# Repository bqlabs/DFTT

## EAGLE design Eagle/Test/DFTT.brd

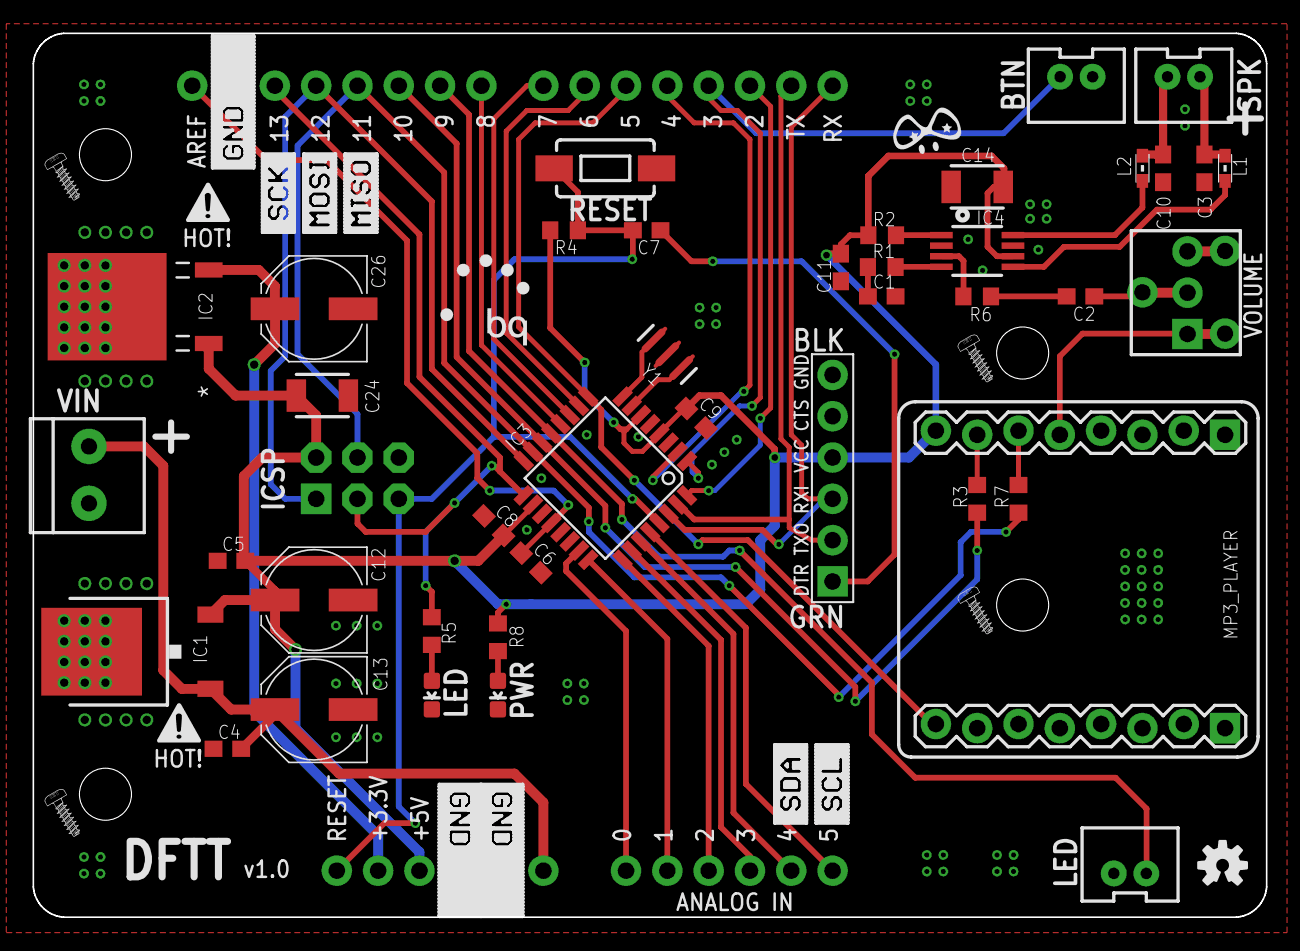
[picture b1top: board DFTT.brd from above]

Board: 2 copper layers, 75.8 x 54.3 mm, 63 parts (1 on the bottom side), 44 nets.

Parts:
BTN: M02JST-PTH-VERT; JST-2-PTH-VERT
C1, C2: 1uF; C0603
C3, C10: 220pF; C0603
C4, C5, C6, C7, C8, C9: 0.1uF; C0603
C11: 10uF; C0603
C12: 10uF; PANASONIC_D
C13, C26: 100uF; PANASONIC_D
C14, C24: 0.1uF; 1210
IC1: 7805DT; TO252
IC2: LF33ABDT-TR; TO228P972X240-3N
IC3: ATMEGA328P; TQFP32-08
IC4: PAM8302AASCR; MSOP8_0.65MM
ICSP: SPI_PRG; 2X3-NS
JP2: 1X08_LOCK
JP3: FTDI_DEVICE; FTDI_DEVICE_SIDE
L1, L2: Ferrite; 0603
LED: M02JST-PTH-VERT; JST-2-PTH-VERT
LOGO3: OSHW-LOGOS; OSHW-LOGO-S
MP3_PLAYER: 1X08_LOCK
PWR: USR; LED-0603
R1, R6: 100; R0603
R2: 10K; R0603
R3, R7: 1K; R0603
R4: 100K; R0603
R5, R8: 330; R0603
R9: 3362U-2
RESET: RESET; TACTILE-SWITCH-1101NE
RV1: VOLUME; TRIM_POT
SPK: M02JST-PTH-VERT; JST-2-PTH-VERT
U3: SHIELD; DUEMILANOVE_VIAS
U$1, U$2, U$3: S_KICIK_GND_2
U$4: S_SCL
U$5: S_SDA
U$6: TROLLFACE
U$7, U$11: S_ATTENTION
U$8: S_MISO
U$9: S_MOSI
U$10: S_SCK
U$12, U$13, U$14, U$15: SCREW
U$22: BQ_LOGO_SMALL
U$23: PIGHIXXX_LOGO
USR: USR; LED-0603
VIN: TERMBLOCK_1X2-3.5MM
Y1: 16MHZ; RESONATOR-SMD

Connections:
3.3V: C26.+, IC2.3, U3.3.3V
5V: C5.2, C8.1, C9.1, C11.2, C12.+, C14.1, C24.1, IC1.2, IC2.1, IC3.4, IC3.6, IC3.18, IC4.6, ICSP.2, JP3.P$4, MP3_PLAYER.8, R2.2, R4.2, R8.2, U3.5V
AD0: IC3.23, U3.A0
AD1: IC3.24, U3.A1
AD2: IC3.25, U3.A2
AD3: IC3.26, U3.A3
AD4: IC3.27, U3.A4
AD5: IC3.28, U3.A5
AREF: C6.1, IC3.20, U3.AREF
AUDIO: MP3_PLAYER.5, R9.1, RV1.2
DTR: C7.1, JP3.P$1
GND: BTN.1, C1.1, C3.1, C4.1, C5.1, C6.2, C8.2, C9.2, C10.1, C11.1, C12.-, C13.-, C14.2, C24.2, C26.-, IC1.3, IC2.2, IC3.3, IC3.5, IC3.21, IC4.7, ICSP.6, JP2.2, JP3.P$5, JP3.P$6, LED.1, MP3_PLAYER.2, PWR.C, R9.3, RESET.1, RV1.3, U3.GND@0, U3.GND@1, U3.GND@2, USR.C, VIN.1, Y1.2
IO2: IC3.32, U3.D2
IO3: BTN.2, IC3.1, U3.D3
IO4: IC3.2, U3.D4
IO5: IC3.9, JP2.8, U3.D5
IO6: IC3.10, U3.D6
IO7: IC3.11, U3.D7
IO8: IC3.12, U3.D8
IO9: IC3.13, LED.2, U3.D9
IO10: IC3.14, R3.1, U3.D10
IO11: IC3.15, ICSP.4, R7.1, U3.D11
IO12: IC3.16, ICSP.1, U3.D12
IO13: IC3.17, ICSP.3, R5.2, U3.D13
unnamed: IC4.4, R1.1
unnamed: IC4.3, R6.1
unnamed: C2.2, R6.2
unnamed: C1.2, R1.2
unnamed: IC4.8, L2.1
unnamed: IC4.5, L1.1
unnamed: R5.1, USR.A
unnamed: PWR.A, R8.1
unnamed: IC3.7, Y1.1
unnamed: IC3.8, Y1.3
RST: C7.2, IC3.29, ICSP.5, R4.1, RESET.2, U3.RES
RV: C2.1, R9.2, RV1.1
RX: IC3.30, JP3.P$3, U3.RX
RXL: MP3_PLAYER.6, R7.2
SD: IC4.1, R2.1
TX: IC3.31, JP3.P$2, U3.TX
TXL: MP3_PLAYER.7, R3.2
VIN: C4.2, C13.+, IC1.1, U3.VIN, VIN.2
VO+: C3.2, L1.2, SPK.1
VO-: C10.2, L2.2, SPK.2

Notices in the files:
parts and their libraries:
microbuilder: This work is placed in the public domain, and may be freely used for commercial and non-commercial work with the following conditions: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
SparkFun-Connectors: Licensing: Creative Commons ShareAlike 4.0 International - https://creativecommons.org/licenses/by-sa/4.0
